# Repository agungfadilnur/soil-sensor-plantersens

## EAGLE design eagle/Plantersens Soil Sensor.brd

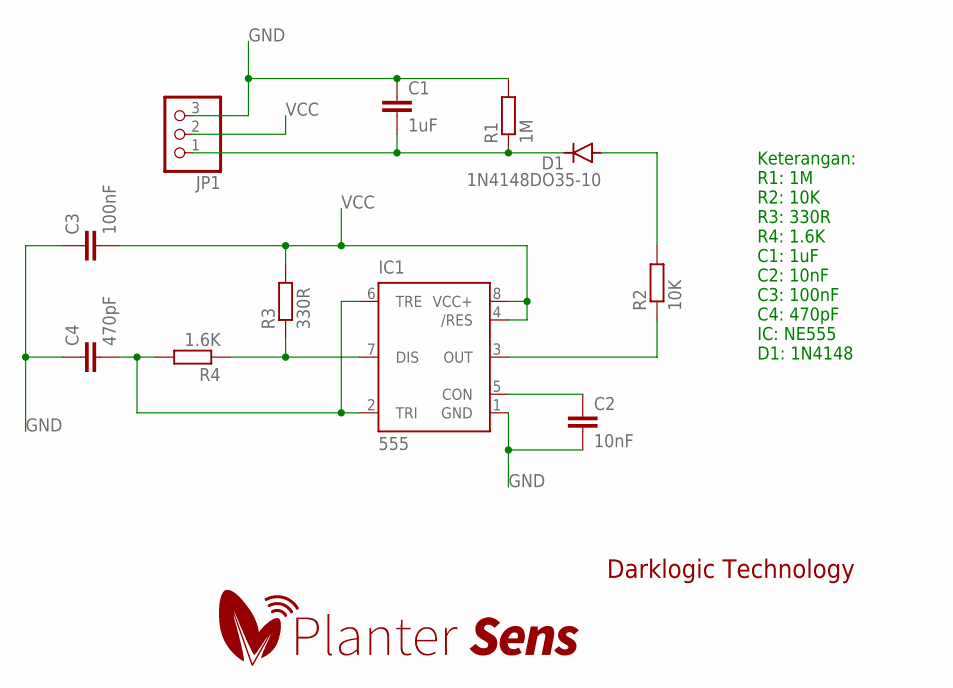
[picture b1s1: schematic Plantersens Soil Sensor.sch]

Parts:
C1: 1uF; C2.5-2
C2: 10nF; C2.5-2
C3: 100nF; C2.5-2
C4: 470pF; C2.5-2
D1: 1N4148DO35-10; DO35-10
IC1: 555; DIP08-KIT
JP1: PINHD-1X3; 1X03
R1: 1M; 0207/10
R2: 10K; 0207/10
R3: 330R; 0207/10
R4: 1.6K; 0207/10

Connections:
GND: C1.1, C2.2, C3.1, C4.1, IC1.1 (GND), JP1.3, R1.2
unnamed: D1.A, R2.2
unnamed: IC1.3 (OUT), R2.1
unnamed: IC1.7 (DIS), R3.1, R4.1
unnamed: C2.1, IC1.5 (CON)
unnamed: C4.2, IC1.2 (TRI), IC1.6 (TRE), R4.2
SIG: C1.2, D1.C, JP1.1, R1.1
VCC: C3.2, IC1.4 (/RES), IC1.8 (VCC+), JP1.2, R3.2

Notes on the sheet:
Keterangan: R1: 1M R2: 10K R3: 330R R4: 1.6K C1: 1uF C2: 10nF C3: 100nF C4: 470pF IC: NE555 D1: 1N4148
Darklogic Technology

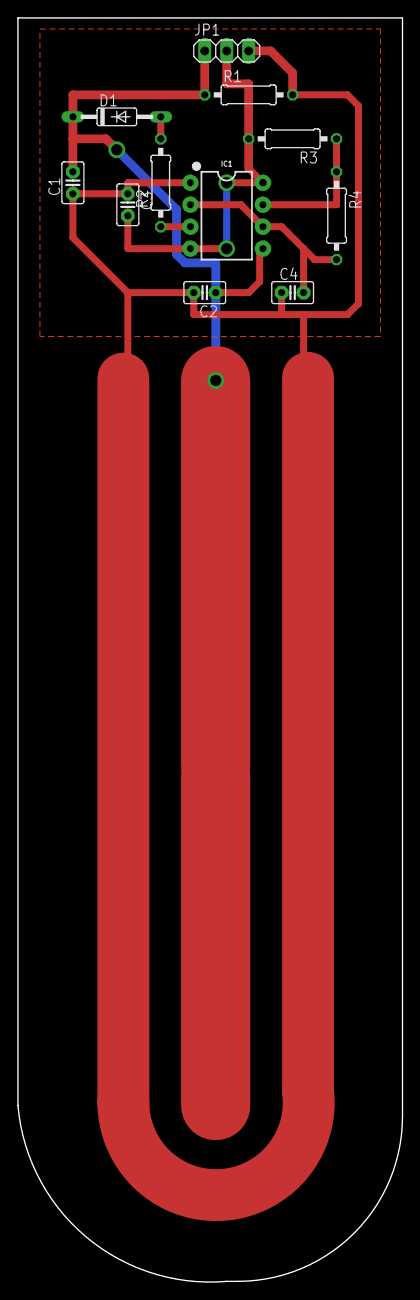
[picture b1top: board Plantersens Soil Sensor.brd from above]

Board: 2 copper layers, 44.4 x 146.1 mm, 11 parts (0 on the bottom side), 8 nets.

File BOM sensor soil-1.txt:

Keterangan:
R1: 1M
R2: 10K
R3: 330R
R4: 1.6K
C1: 1uF
C2: 10nF
C3: 100nF
C4: 470pF
IC: NE555
D1: 1N4148

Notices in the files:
parts and their libraries:
SparkFun-IC-Special-Function: Licensing: Creative Commons ShareAlike 4.0 International - https://creativecommons.org/licenses/by-sa/4.0
